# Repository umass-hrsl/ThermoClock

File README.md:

Arduino script, CAD design, PCB design associated with the Manuscript titled "Around the ThermoClock: A Precision Automated Temperature Control System for Ex Vivo Studies" by Kaiyin(Kelly) Zhang, Dominic Locurto, Matthew Belden, Mark A Price, Cathal J Kearney and Meghan E Huber

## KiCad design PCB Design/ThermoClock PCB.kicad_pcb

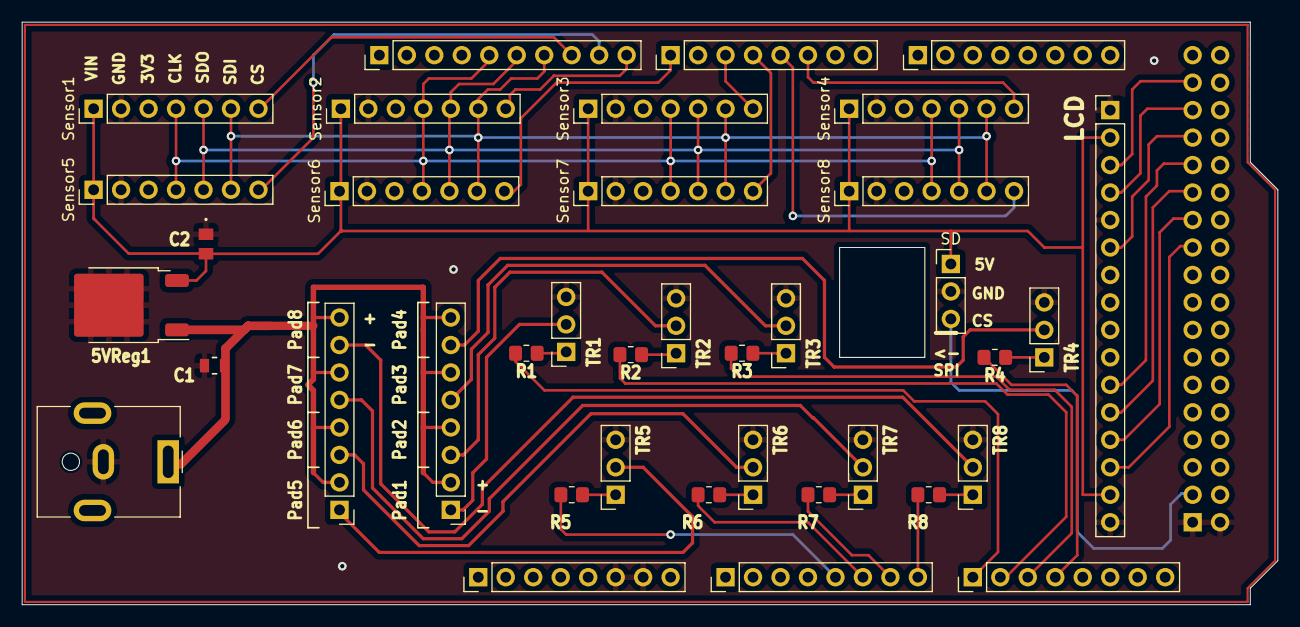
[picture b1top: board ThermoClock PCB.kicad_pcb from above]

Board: 2 copper layers, 116.1 x 53.8 mm, 39 parts (1 on the bottom side), 47 nets.

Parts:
5VReg1: LM78M05_TO252; TO-252-2
C1: C; CAP_CL21_SAM
C2: C; CAP_0805_B_WAL
J1: Jack-DC; BarrelJack_CUI_PJ-063AH_Horizontal
LED1: Conn_01x16_Male; PinHeader_1x16_P2.54mm_Vertical
P1: Power; PinHeader_1x08_P2.54mm_Vertical
P2, P3: Analog; PinHeader_1x08_P2.54mm_Vertical
P4: Digital; PinHeader_2x18_P2.54mm_Vertical
P5: PWM; PinHeader_1x10_P2.54mm_Vertical
P6: PWM; PinHeader_1x08_P2.54mm_Vertical
P7: Communication; PinHeader_1x08_P2.54mm_Vertical
PAD1-1, PAD5-1: Conn_01x08_Male; PinHeader_1x08_P2.54mm_Vertical
R1, R2, R3, R4, R5, R6, R7, R8: R; R_0805_2012Metric_Pad1.20x1.40mm_HandSolder
SD: Conn_01x03; PinHeader_1x03_P2.54mm_Vertical
Sensor1, Sensor2, Sensor3, Sensor4, Sensor5, Sensor6, Sensor7, Sensor8: Conn_01x07; PinHeader_1x07_P2.54mm_Vertical
TR1, TR2, TR3, TR4, TR5, TR6, TR7, TR8: Conn_01x03; PinSocket_1x03_P2.54mm_Vertical

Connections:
+5V: P1.5, P4.35, P4.36
+12V: 5VReg1.1 (VI), C1.2, J1.1, PAD1-1.2, PAD1-1.4, PAD1-1.6, PAD1-1.8, PAD5-1.2, PAD5-1.4, PAD5-1.6, PAD5-1.8
/2(**): P6.6, Sensor4.7
/3(**): P6.5, Sensor8.7
/4(**): P6.4, Sensor7.7
/5(**): P6.3, Sensor3.7
/7(**): P6.1, Sensor6.7
/8(**): P5.10, Sensor2.7
/9(**): P5.9, Sensor5.7
/10(**): P5.8, Sensor1.7
/11(**): P5.7, Sensor1.6, Sensor2.6, Sensor3.6, Sensor4.6, Sensor5.6, Sensor6.6, Sensor7.6, Sensor8.6
/12(**): P5.6, Sensor1.5, Sensor2.5, Sensor3.5, Sensor4.5, Sensor5.5, Sensor6.5, Sensor7.5, Sensor8.5
/13(**): P5.5, Sensor1.4, Sensor2.4, Sensor3.4, Sensor4.4, Sensor5.4, Sensor6.4, Sensor7.4, Sensor8.4
/22: LED1.3, P4.33
/24: LED1.4, P4.31
/26: LED1.6, P4.29
/28: LED1.11, P4.27
/30: LED1.12, P4.25
/32: LED1.13, P4.23
/34: LED1.14, P4.21
/52(CS): P4.3, SD.3
/A4: P2.5, R5.2
/A5: P2.6, R6.2
/A6: P2.7, R7.2
/A7: P2.8, R8.2
/A8: P3.1, R1.2
/A9: P3.2, R2.2
/A10: P3.3, R3.2
/A11: P3.4, R4.2
/Pad1: PAD1-1.1, TR1.2
/Pad2: PAD1-1.3, TR2.2
/Pad3: PAD1-1.5, TR3.2
/Pad4: PAD1-1.7, TR4.2
/Pad5: PAD5-1.1, TR5.2
/Pad6: PAD5-1.3, TR6.2
/Pad7: PAD5-1.5, TR7.2
/Pad8: PAD5-1.7, TR8.2
/VCC5: 5VReg1.3 (VO), C2.2, LED1.2, LED1.15, SD.1, Sensor1.1, Sensor2.1, Sensor3.1, Sensor4.1, Sensor5.1, Sensor6.1, Sensor7.1, Sensor8.1
GND: 5VReg1.2 (GND), C1.1, C2.1, J1.2, LED1.1, LED1.5, LED1.16, P1.6, P1.7, P4.1, P4.2, P5.4, SD.2, Sensor1.2, Sensor2.2, Sensor3.2, Sensor4.2, Sensor5.2, Sensor6.2, Sensor7.2, Sensor8.2, TR1.3, TR2.3, TR3.3, TR4.3, TR5.3, TR6.3, TR7.3, TR8.3
unnamed: R1.1, TR1.1
unnamed: R2.1, TR2.1
unnamed: R3.1, TR3.1
unnamed: R4.1, TR4.1
unnamed: R5.1, TR5.1
unnamed: R6.1, TR6.1
unnamed: R7.1, TR7.1
unnamed: R8.1, TR8.1

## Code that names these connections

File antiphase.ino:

#include <Adafruit_MAX31865.h>  

#include <PID_v1.h>  

#include <SD.h>  

 

//Temperature control system with 5 pads 
//particular version to capsure antiphase entrainment and multiple entrainment schedules
 

// Define the RREF value for the RTD Temperature Sensors 

// Use 430.0 for PT100 and 4300.0 for PT1000  

#define RREF 430.0  

// The nominal 0-degrees-C resistance of the sensor  

// 100.0 for PT100, 1000.0 for PT1000  

#define RNOMINAL 100.35 

#define RNOMINAL_2 100.15  

#define RNOMINAL_3 100.15  

#define RNOMINAL_4 100.25  

#define RNOMINAL_5 100.1  

//#define RNOMINAL_6 100  



 

// Define Arduino pin numbers for the RTD Temperature Sensors  

// in the following order: CS, DI, DO, CLK  

 

Adafruit_MAX31865 sensor1 = Adafruit_MAX31865(10, 11, 12, 13); //J3 

Adafruit_MAX31865 sensor2 = Adafruit_MAX31865(8, 11, 12, 13); //J5 

Adafruit_MAX31865 sensor3 = Adafruit_MAX31865(5, 11, 12, 13); //J8 

Adafruit_MAX31865 sensor4 = Adafruit_MAX31865(2, 11, 12, 13); //J10 

Adafruit_MAX31865 sensor5 = Adafruit_MAX31865(9, 11, 12, 13); //J4 



 

unsigned long lastRead = 0UL;  

 

unsigned long startTime = millis();  

 

//PID SETUP  

 

double setpoint1,setpoint2,setpoint3,setpoint4,setpoint5,setpoint6; 

double input1,input2,input3,input4,input5,input6; 

double output1,output2,output3,output4,output5,output6; 

 

 

//Define Arduino pin numbers for the heating pads outputs  

 

#define pwmPin1 A8 //Pad1 

#define pwmPin2 A9 //Pad2 

#define pwmPin3 A10 //Pad3 

#define pwmPin4 A11 //Pad4 

#define pwmPin5 A4 //Pad5 

//#define pwmPin6 A5 //Pad6 


 

 

double kp = 300; //proportional gain  190 for one pad 

 

double ki = 1.7; //integral gain  1.2 for one pad

 

double kd = 9; //derivative gain  15 for one pad 

 

 

PID myPID1(&input1, &output1, &setpoint1,kp,ki,kd, DIRECT); //setup PID  

PID myPID2(&input2, &output2, &setpoint2,kp,ki,kd, DIRECT); //setup PID  

PID myPID3(&input3, &output3, &setpoint3,kp,ki,kd, DIRECT); //setup PID  

PID myPID4(&input4, &output4, &setpoint4,kp,ki,kd, DIRECT); //setup PID  

PID myPID5(&input5, &output5, &setpoint5,kp,ki,kd, DIRECT); //setup PID  

//PID myPID6(&input6, &output6, &setpoint6,kp,ki,kd, DIRECT); //setup PID  



 

 

long now = 0; //initialize current time variable  

 

 

//File Object Initialization  

 

File dataFile;  

 





 

 

void setup()  

 

{  

 

Serial.begin(9600);  

 

sensor1.begin(MAX31865_3WIRE); //using 3-wire RTD sensor  

sensor2.begin(MAX31865_3WIRE);   

sensor3.begin(MAX31865_3WIRE); 

sensor4.begin(MAX31865_3WIRE); 

sensor5.begin(MAX31865_3WIRE);  

//sensor6.begin(MAX31865_3WIRE); 


 

myPID1.SetMode(AUTOMATIC);  

myPID2.SetMode(AUTOMATIC);  

myPID3.SetMode(AUTOMATIC);  

myPID4.SetMode(AUTOMATIC);  

myPID5.SetMode(AUTOMATIC);  

//myPID6.SetMode(AUTOMATIC);  



 

pinMode(pwmPin1, OUTPUT);  

pinMode(pwmPin2, OUTPUT);  

pinMode(pwmPin3, OUTPUT);  

pinMode(pwmPin4, OUTPUT);  

pinMode(pwmPin5, OUTPUT);  

//pinMode(pwmPin6, OUTPUT);  

 

Serial.print("Initializing SD card...");  

 

pinMode(52, OUTPUT);  

 

 

if (!SD.begin(52)) {  

 

Serial.println("initialization failed!");  

 

return;  

 

}  

 

Serial.println("initialization done.");  

 

 

dataFile = SD.open("0628.txt", FILE_WRITE);  

 

}  

 

void loop() {  

 

if (dataFile) {  

 

for (int i = 0; i <= 870000; i++) {  

 

now = millis();  

 

uint16_t rtd1 = sensor1.readRTD();  

uint16_t rtd2 = sensor2.readRTD();  

uint16_t rtd3 = sensor3.readRTD();  

uint16_t rtd4 = sensor4.readRTD();  

uint16_t rtd5 = sensor5.readRTD();  


 

 

float ratio1 = rtd1;  

float ratio2 = rtd2;  

float ratio3 = rtd3;  

float ratio4 = rtd4;  

float ratio5 = rtd5;  



 

ratio1 /= 32768;  

ratio2 /= 32768;  

ratio3 /= 32768;  

ratio4 /= 32768;  

ratio5 /= 32768;  



 
//Convert RTD reading to temperature in degrees celsius
double temp1 = sensor1.temperature(RNOMINAL, RREF);  

double temp2 = sensor2.temperature(RNOMINAL_2, RREF);  

double temp3 = sensor3.temperature(RNOMINAL_3, RREF);  

double temp4 = sensor4.temperature(RNOMINAL_4, RREF);  

double temp5 = sensor5.temperature(RNOMINAL_5, RREF);  

//double temp6 = sensor6.temperature(RNOMINAL_6, RREF);  


 

input1 = mapf(temp1, -50, 280, 0, 255); //map temp value to value read to PWM pin  

input2 = mapf(temp2, -50, 280, 0, 255); //map temp value to value read to PWM pin  

input3 = mapf(temp3, -50, 280, 0, 255); //map temp value to value read to PWM pin  

input4 = mapf(temp4, -50, 280, 0, 255);  

input5 = mapf(temp5, -50, 280, 0, 255); //map temp value to value read to PWM pin  
 

//setpoints for PID 

float desiredtemp1; 

float desiredtemp2; 

float desiredtemp3; 

float desiredtemp4; 

float desiredtemp5; 


setpoint1 = mapf(desiredtemp1, -50, 280, 0 ,255);  

setpoint2 = mapf(desiredtemp2, -50, 280, 0 ,255); 

setpoint3 = mapf(desiredtemp3, -50, 280, 0 ,255);  

setpoint4 = mapf(desiredtemp4, -50, 280, 0 ,255); 

setpoint5 = mapf(desiredtemp5, -50, 280, 0 ,255);  

 

unsigned long currentTime = millis();  

 

unsigned long elapsedTime = currentTime - startTime;  

 

 

myPID1.Compute();  

myPID2.Compute();  

myPID3.Compute();  

myPID4.Compute();  

myPID5.Compute();  

//myPID6.Compute();  


 

//Match heating pad outputs to the corresponding temperature sensor  

analogWrite(pwmPin1, output1);  

analogWrite(pwmPin2, output2);  

analogWrite(pwmPin3, output3);  

analogWrite(pwmPin4, output4);  

analogWrite(pwmPin5, output5);  

//analogWrite(pwmPin6, output6);  



 

if (i%40 == 0){ //this can change depending on how many pad/sensor pair you have running parallel to each other  
dataFile.print(temp1);  
dataFile.print(",");  
dataFile.print(temp2);  
dataFile.print(","); 
dataFile.print(temp3);  
dataFile.print(",");  
dataFile.print(temp4);  
dataFile.print(",");  
dataFile.print(temp5);  
dataFile.print(",");  
dataFile.print(output1);  
dataFile.print(",");  
dataFile.print(output2);  
dataFile.print(","); 
dataFile.print(output3);  
dataFile.print(",");  
dataFile.print(output4);  
dataFile.print(",");  
dataFile.print(output5);  
dataFile.print(",");   
dataFile.println(now);  
Serial.println("half minute passed");  
Serial.println(now);  
Serial.println(i);  

 

 

}  

//define setpoint temperatures and timepoints 

if (i==5){  
desiredtemp1=35; 
desiredtemp2=35; 
desiredtemp3=35; 
desiredtemp4=35; 
desiredtemp5=35; 
}  

if (i==2400){  
desiredtemp1=37; 
desiredtemp2=37; 
desiredtemp3=37; 
desiredtemp4=37; 
desiredtemp5=37; 
}  

if(i==4800){
desiredtemp1=36;
}
if(i==24000){
desiredtemp2=36;
}
if(i==43200){
desiredtemp3=36;
}
if(i==62400){
desiredtemp4=36;
desiredtemp1=38.5;
}
if(i==81600){
desiredtemp5=36;
desiredtemp2=38.5;
}
if(i==100800){
desiredtemp3=38.5;
}
if(i==120000){
desiredtemp4=38.5;
desiredtemp1=36;
}
if(i==139200){
desiredtemp5=38.5;
desiredtemp2=36;
}
if(i==158400){
desiredtemp3=36;
}
if(i==177600){
desiredtemp4=36;
desiredtemp1=38.5;
}
if(i==196800){
desiredtemp5=36;
desiredtemp2=38.5;
}
if(i==216000){
desiredtemp3=38.5;
}
if(i==235200){
desiredtemp4=38.5;
desiredtemp1=36;
}
if(i==254400){
desiredtemp5=38.5;
desiredtemp2=36;
}
if(i==273600){
desiredtemp3=36;
}
if(i==292800){
desiredtemp4=36;
desiredtemp1=38.5;
}
if(i==312000){
desiredtemp5=36;
desiredtemp2=38.5;
}
if(i==331200){
desiredtemp3=38.5;
}
if(i==350400){
desiredtemp4=38.5;
desiredtemp1=37;
}
if(i==369600){
desiredtemp5=38.5;
desiredtemp2=37;
}
if(i==388800){
desiredtemp3=37;
}
if(i==408000){
desiredtemp4=37;
}
if(i==427200){
desiredtemp5=37;
}






Serial.print(temp1);  
Serial.print(",");  
Serial.print(temp2);  
Serial.print(",");  
Serial.print(temp3);  
Serial.print(",");  
Serial.print(temp4);  
Serial.print(",");  
Serial.print(temp5); 
Serial.print(","); 
Serial.println();  
Serial.print(output1);  
Serial.print(",");  
Serial.print(output2);  
Serial.print(",");  
Serial.print(output3);  
Serial.print(",");  
Serial.print(output4);  
Serial.print(",");  
Serial.print(output5); 
Serial.print(",");  



 

 

 

// Serial.println(output);  

 

// Serial.print(",");  

 

// Serial.print(input);  

 

// Serial.print(",");  

 

// Serial.print(",");  

 

Serial.println(millis());  

 

dataFile.flush();  

 

 

// if (error < 2) {  

 

// myPID.SetTunings(10, 0, 0);  

 

// status = "cons";  

 

// }  

 

// else{  

 

// myPID.SetTunings(kp, ki, kd);  

 

// status ="agg";  

 

// }  

 

//Serial.println(status);  

 

}  

 

dataFile.close();  

 

Serial.println("protocol done");  

 

}  

 

}  

 

//map function for decimals  

 

double mapf(double val, double in_min, double in_max, double out_min, double out_max) {  

 

return (val - in_min) * (out_max - out_min) / (in_max - in_min) + out_min; }  

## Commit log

2021-05-24 First Code Commit - converting Arduino (C/C++) to python
    First commit of converting Arduino (C/C++) to python for Raspberry Pi. Needs continued work to finish sensor pins and testing for temperature pid controller.
2021-05-24 Organization
    Organizing files and folders.
2021-07-14 Create PhysicalUI.py
    Untested, preliminary code for user control and interface.
2022-10-02 code for more complete system w/ scheduling, temperature control etc and for arduino
2022-10-02 single pad testing code
2022-10-12 uploaded libraries
2022-11-17 Revert "Single pad test"
2022-11-22 Updated Lunch Tray Code
2023-02-20 warming tray version 2 uploaded
    under development -- file initialization
2023-02-22 PCB update
2023-02-22 PID Controller creation& tuning
2023-02-22 PCB Update: added transistors and pinouts
2023-02-23 Added some libraries to project for potential use
    Digikey footprints for some parts (general one plus a transistor)
2023-02-24 small changes
2023-02-24 library added
2023-02-24 Added footprints for transistor pins and surface mount resistors
2023-02-28 added traces to pcb
2023-03-01 updated resistor footprint
2023-03-04 Slight code changes
2023-03-07 PCB & Code
    PCB: added 0805 footprints for resistors and capacitors
    Code: testing controllers again so gains are being changed
2023-03-22 Lots of controller changes
2023-04-19 Changed some setpoints around for testing - no major changes
2023-04-19 Added PID Testing files
    Excel Sheets and Pictures for all trials thus far
2023-04-19 Test code for multiple RTD sensors
2023-07-17 Large Update of all files
2024-07-01 README.md
2024-07-01 Add files via upload
    Arduino IDE sketch for running one-pad Bioclockbot. The default temperature is the 72h 36C(12h)<->38.5C(12h) temperature cycle in Buhr et al.(2010)
2024-07-01 Onepad_75h+.ino
2024-07-01 Rename onepad_75h+.ino to onepad_72h.ino
2024-07-17 Prep for Final Version
2025-02-21 Update 02212025
2025-07-21 sensor pin correction
2025-08-18 RTD sensor 3 pin correction
